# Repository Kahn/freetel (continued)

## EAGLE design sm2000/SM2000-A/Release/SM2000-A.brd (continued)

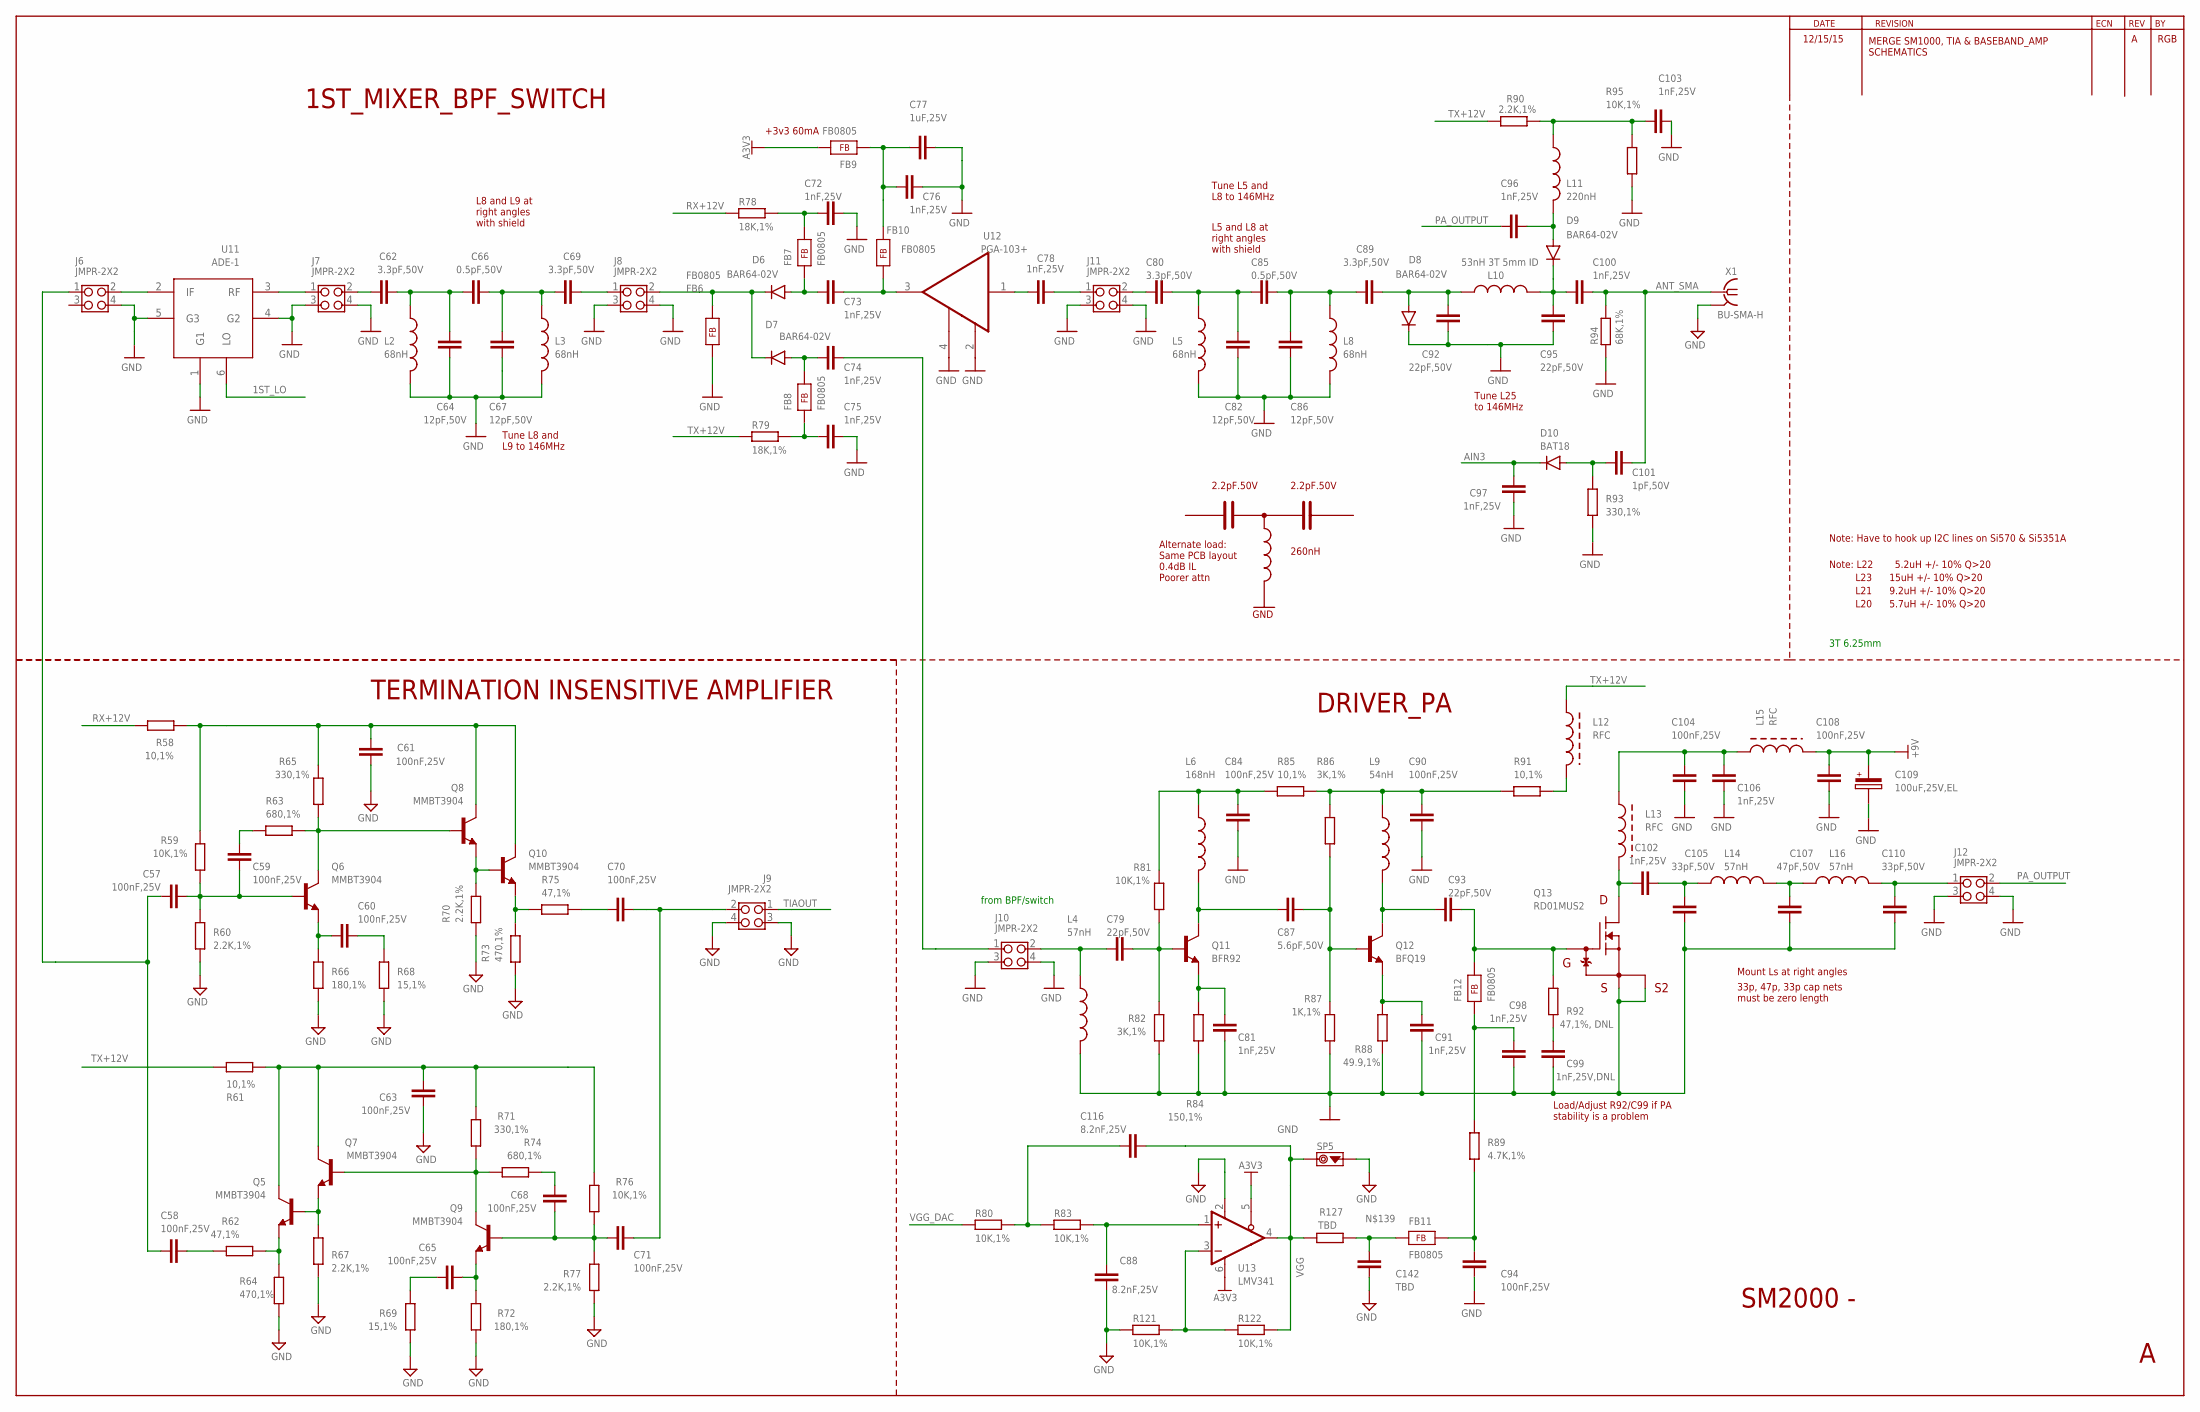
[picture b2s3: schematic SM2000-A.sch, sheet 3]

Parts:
C57, C58, C59, C60, C61, C63, C65, C68, C70, C71, C84, C90, C94, C104, C108: 100nF,25V; C0805
C62, C69, C80, C89: 3.3pF,50V; C0805
C64, C67, C82, C86: 12pF,50V; C0805
C66, C85: 0.5pF,50V; C0805
C72, C73, C74, C75, C76, C78, C81, C91, C96, C97, C98, C100, C102, C103, C106: 1nF,25V; C0805
C77: 1uF,25V; C0805
C79, C92, C93, C95: 22pF,50V; C0805
C87: 5.6pF,50V; C0805
C88, C116: 8.2nF,25V; C0805
C99: 1nF,25V,DNL; C0805
C101: 1pF,50V; C0805
C105, C110: 33pF,50V; C0805
C107: 47pF,50V; C0805
C109: 100uF,25V,EL; CAP-CHEMI-F80
C142: TBD; C0805
D6, D7, D8, D9: BAR64-02V; SC79_INFINEON
D10: BAT18; SOT23
FB6, FB7, FB8, FB9, FB10, FB11, FB12: FB0805; FE0805
J6, J7, J8, J9, J10, J11, J12: JMPR-2X2; JMPR-2X2X.1
L2, L3, L5, L8: 68nH; L10X15
L4, L14, L16: 57nH; L10X15
L6: 168nH; L10X15
L9: 54nH; L10X15
L10: 53nH 3T 5mm ID; L10X15
L11: 220nH; L10X15
L12, L13, L15: RFC; Z15/4
Q5, Q6, Q7, Q8, Q9, Q10: MMBT3904; SOT23
Q11: BFR92; SOT23
Q12: BFQ19; SOT89
Q13: RD01MUS2; SOT89
R58, R61, R85, R91: 10,1%; R0805
R59, R76, R80, R81, R83, R95, R121, R122: 10K,1%; R0805
R60, R67, R70, R77, R90: 2.2K,1%; R0805
R62, R75: 47,1%; R0805
R63, R74: 680,1%; R0805
R64, R73: 470,1%; R0805
R65, R71, R93: 330,1%; R0805
R66, R72: 180,1%; R0805
R68, R69: 15,1%; R0805
R78, R79: 18K,1%; R0805
R82, R86: 3K,1%; R0805
R84: 150,1%; R0805
R87: 1K,1%; R0805
R88: 49.9,1%; R0805
R89: 4.7K,1%; R0805
R92: 47,1%, DNL; R0805
R94: 68K,1%; R0805
R127: TBD; R0805
SP5: SCOPE_PAD
U11: ADE-1
U12: PGA-103+; DF782
U13: LMV341; SOT23-6
X1: BU-SMA-H

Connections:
1ST_LO: U11.6 (LO); also elsewhere on the board
+9V: C108.1, C109.1, L15.2; also elsewhere on the board
A3V3: FB9.2, U13.5 (!SHDN!), U13.6 (V+); also elsewhere on the board
AIN3: C97.2, D10.1 (K); also elsewhere on the board
ANT_SMA: C100.1, C101.2, R94.2, X1.1
DRIVER/PA_INPUT: C74.2, J10.1
GND: C61.2, C63.2, C64.2, C67.1, C72.2, C75.2, C76.2, C77.2, C81.2, C82.2, C84.2, C86.1, C88.2, C90.2, C91.2, C92.2, C94.2, C95.2, C97.1, C98.2, C99.2, C103.2, C104.2, C105.2, C106.2, C107.2, C108.2, C109.2, C110.2, C142.2, D8.C, FB6.1, J6.4, J7.3, J7.4, J8.3, J8.4, J9.3, J9.4, J10.3, J10.4, J11.3, J11.4, J12.3, J12.4, L2.2, L3.2, L4.2, L5.2, L8.2, Q13.2 (S), Q13.4 (S2), R60.1, R64.1, R66.1, R67.1, R68.1, R69.1, R70.1, R72.1, R73.1, R77.1, R82.1, R84.1, R87.1, R88.1, R93.1, R94.1, R95.1, R121.1, SP5.2, U11.1 (G1), U11.4 (G2), U11.5 (G3), U12.2 (GND), U12.4 (GND1), U13.2 (GND), X1.2, X1.3 (2), X1.4 (2), X1.5 (2); also elsewhere on the board
unnamed: C76.1, C77.1, FB9.1, FB10.2
unnamed: R121.2, R122.1, U13.3 (-IN)
unnamed: C107.1, L14.2, L16.1
unnamed: C80.2, J11.2
unnamed: J6.2, U11.2 (IF)
unnamed: L12.2, R91.1
unnamed: C62.1, C64.1, C66.2, L2.1
unnamed: C116.1, R80.2, R83.1
unnamed: C102.1, L13.2, Q13.3 (D)
unnamed: C93.1, FB12.2, Q13.1 (G), R92.2
unnamed: C88.1, R83.2, U13.1 (+IN)
unnamed: C95.1, C100.2, D9.C, L10.2
unnamed: C94.1, FB11.2, R89.1
unnamed: C110.1, J12.1, L16.2
unnamed: C62.2, J7.2
unnamed: C101.1, D10.3 (A), R93.2
unnamed: J7.1, U11.3 (RF)
unnamed: C78.2, J11.1
unnamed: C78.1, U12.1 (1N)
unnamed: C70.1, C71.2, J9.2
unnamed: Q6.3 (C), Q8.1 (B), R63.2, R65.2
unnamed: C61.1, Q8.3 (C), Q10.3 (C), R58.1, R59.2, R65.1
unnamed: Q8.2 (E), Q10.1 (B), R70.2
unnamed: C59.1, R63.1
unnamed: C81.1, Q11.2 (E), R84.2
unnamed: C91.1, Q12.3 (E), R88.2
unnamed: C84.1, L6.1, R81.2, R85.2
unnamed: C90.1, L9.1, R85.1, R86.2, R91.2
unnamed: C87.1, Q12.1 (B), R86.1, R87.2
unnamed: C79.1, Q11.1 (B), R81.1, R82.2
unnamed: C69.1, J8.1
unnamed: C87.2, L6.2, Q11.3 (C)
unnamed: C57.1, C59.2, Q6.1 (B), R59.1, R60.2
unnamed: C93.2, L9.2, Q12.2 (C), Q12.4 (C)
unnamed: C60.1, Q6.2 (E), R66.2
unnamed: C60.2, R68.2
unnamed: Q10.2 (E), R73.2, R75.1
unnamed: C70.2, R75.2
unnamed: Q7.1 (B), Q9.3 (C), R71.2, R74.2
unnamed: C63.1, Q5.3 (C), Q7.3 (C), R61.2, R71.1, R76.2
unnamed: Q5.1 (B), Q7.2 (E), R67.2
unnamed: C68.1, R74.1
unnamed: C68.2, C71.1, Q9.1 (B), R76.1, R77.2
unnamed: C65.1, Q9.2 (E), R72.2
unnamed: C65.2, R69.2
unnamed: Q5.2 (E), R62.1, R64.2
unnamed: C58.2, R62.2
unnamed: C72.1, FB7.2, R78.2
unnamed: C79.2, J10.2, L4.1
unnamed: C99.1, R92.1
unnamed: C98.1, FB12.1, R89.2
unnamed: C73.1, D6.A, FB7.1
unnamed: C73.2, FB10.1, U12.3 (OUT)
unnamed: C74.1, D7.A, FB8.2
unnamed: C102.2, C105.1, L14.1
unnamed: C75.1, FB8.1, R79.2
unnamed: C66.1, C67.2, C69.2, L3.1
unnamed: C104.1, C106.1, L13.1, L15.1
unnamed: D6.C, D7.C, FB6.2, J8.2
unnamed: C80.1, C82.1, C85.2, L5.1
unnamed: C85.1, C86.2, C89.2, L8.1
unnamed: C142.1, FB11.1, R127.1
unnamed: C89.1, C92.1, D8.A, L10.1
unnamed: C96.1, D9.A, L11.2
unnamed: C103.1, L11.1, R90.1, R95.2
PA_OUTPUT: C96.2, J12.2
RX+12V: R58.2, R78.1; also elsewhere on the board
TIAIN: C57.2, C58.1, J6.1
TIAOUT: J9.1; also elsewhere on the board
TX+12V: L12.1, R61.1, R79.1, R90.2; also elsewhere on the board
VGG: C116.2, R122.2, R127.2, SP5.1, U13.4 (OUT)
VGG_DAC: R80.1; also elsewhere on the board

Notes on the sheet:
SM2000 -
12/15/15
MERGE SM1000, TIA & BASEBAND_AMP SCHEMATICS
RGB
3T 6.25mm
Note: L22
5.2uH +/- 10% Q>20
L23 15uH +/- 10% Q>20
L21 9.2uH +/- 10% Q>20
L20 5.7uH +/- 10% Q>20
Note: Have to hook up I2C lines on Si570 & Si5351A
Tune L8 and L9 to 146MHz
+3v3 60mA
Alternate load: Same PCB layout 0.4dB IL Poorer attn
Tune L5 and L8 to 146MHz
L5 and L8 at right angles with shield
L8 and L9 at right angles with shield
Tune L25 to 146MHz
1ST_MIXER_BPF_SWITCH
TERMINATION INSENSITIVE AMPLIFIER
Load/Adjust R92/C99 if PA stability is a problem
from BPF/switch
33p, 47p, 33p cap nets must be zero length
Mount Ls at right angles
DRIVER_PA
GND
2.2pF.50V
260nH

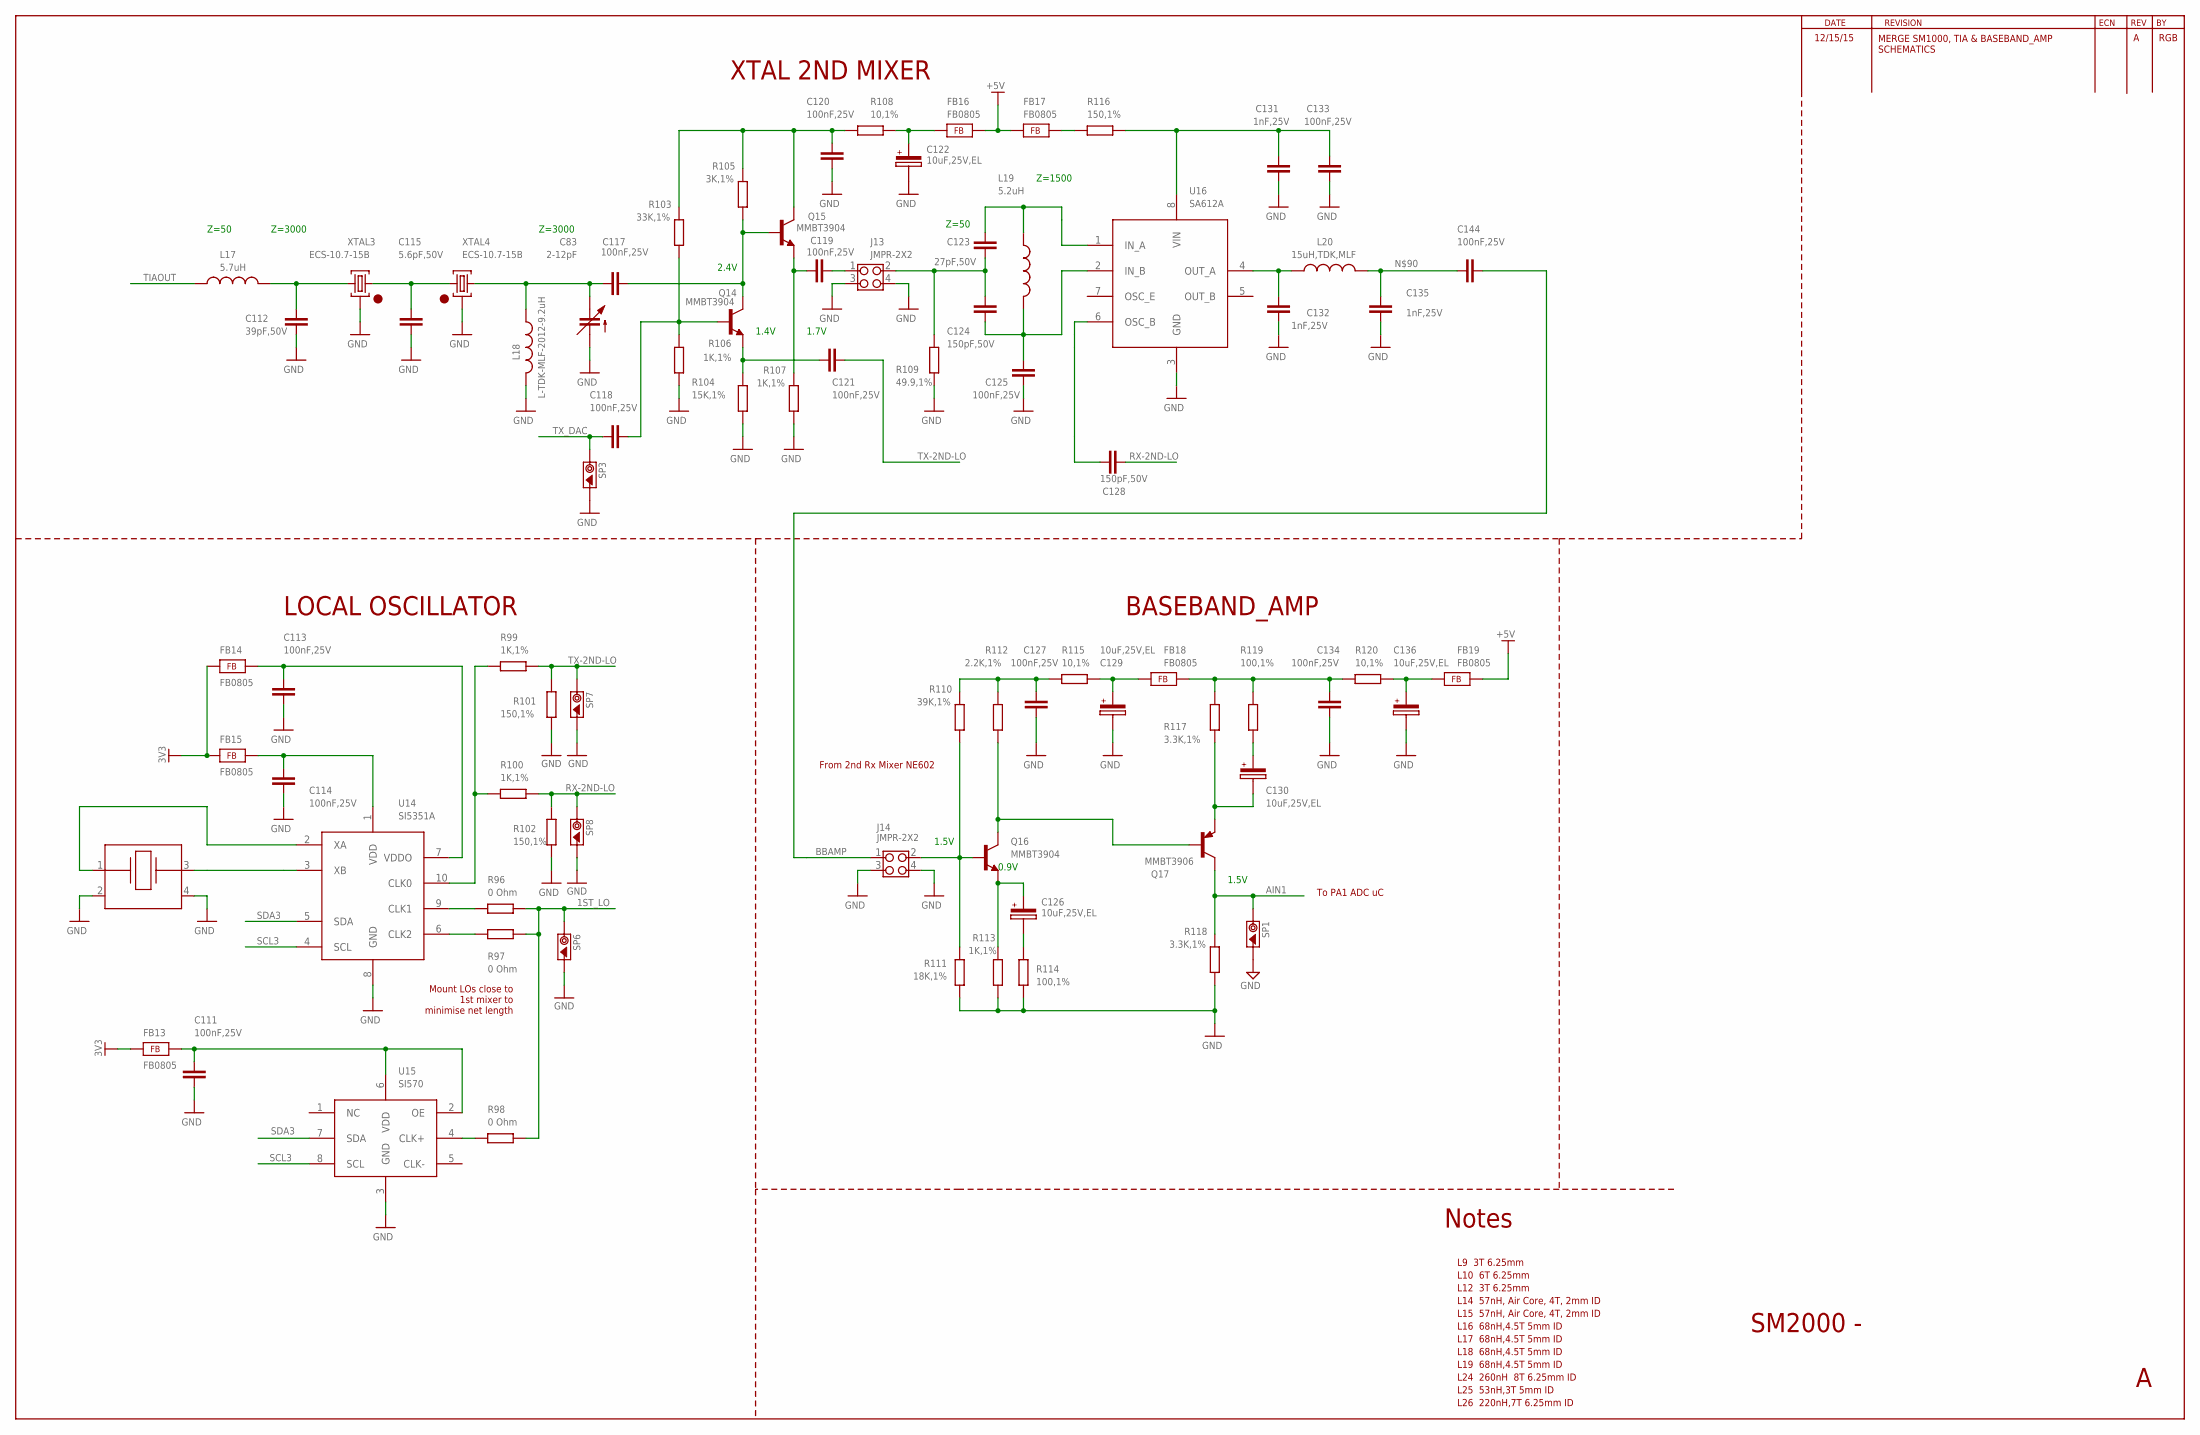
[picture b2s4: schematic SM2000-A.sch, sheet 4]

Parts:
C83: 2-12pF; TRIMCAP_VAR_2222_V
C111, C113, C114, C117, C118, C119, C120, C121, C125, C127, C133, C134, C144: 100nF,25V; C0805
C112: 39pF,50V; C0805
C115: 5.6pF,50V; C0805
C122, C126, C129, C130, C136: 10uF,25V,EL; NICHICON-WJ-5
C123: 27pF,50V; C0805
C124, C128: 150pF,50V; C0805
C131, C132, C135: 1nF,25V; C0805
FB13, FB14, FB15, FB16, FB17, FB18, FB19: FB0805; FE0805
J13, J14: JMPR-2X2; JMPR-2X2X.1
L17: 5.7uH; L-TDK-MLF2012
L18: L-TDK-MLF-2012-9.2uH; L-TDK-MLF2012
L19: 5.2uH; L-TDK-MLF2012
L20: 15uH,TDK,MLF; L-TDK-MLF2012
Q14, Q15, Q16: MMBT3904; SOT23
Q17: MMBT3906; SOT23
R96, R97, R98: 0 Ohm; R0805
R99, R100, R106, R107, R113: 1K,1%; R0805
R101, R102, R116: 150,1%; R0805
R103: 33K,1%; R0805
R104: 15K,1%; R0805
R105: 3K,1%; R0805
R108, R115, R120: 10,1%; R0805
R109: 49.9,1%; R0805
R110: 39K,1%; R0805
R111: 18K,1%; R0805
R112: 2.2K,1%; R0805
R114, R119: 100,1%; R0805
R117, R118: 3.3K,1%; R0805
SP1, SP3, SP6, SP7, SP8: SCOPE_PAD
U14: SI5351A; MSOP10
U15: SI570
U16: SA612A; SO-08
XTAL2: 25.000MHz; CTS-405
XTAL3, XTAL4: ECS-10.7-15B; HC49U

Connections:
1ST_LO: R96.1, R97.1, R98.1, SP6.1; also elsewhere on the board
3V3: FB13.1, FB14.1, FB15.1; also elsewhere on the board
+5V: FB16.2, FB17.1, FB19.2; also elsewhere on the board
AIN1: Q17.3 (C), R118.2, SP1.1; also elsewhere on the board
BBAMP: C144.1, J14.1
GND: C83.R1 (R), C83.R2 (R), C111.2, C112.2, C113.2, C114.2, C115.2, C120.2, C122.2, C125.1, C127.2, C129.2, C131.1, C132.1, C133.1, C134.2, C135.1, C136.2, J13.3, J13.4, J14.3, J14.4, L18.P$2 (2), R101.2, R102.2, R104.1, R106.1, R107.1, R109.1, R111.1, R113.1, R114.1, R118.1, SP1.2, SP3.2, SP6.2, SP7.2, SP8.2, U14.8 (GND), U15.3 (GND), U16.3 (GND), XTAL2.2, XTAL2.4, XTAL3.2, XTAL4.2; also elsewhere on the board
unnamed: U14.2 (XA), XTAL2.1
unnamed: C119.2, J13.1
unnamed: C114.1, FB15.2, U14.1 (VDD)
unnamed: C123.1, C124.2, J13.2, R109.2
unnamed: C124.1, C125.2, L19.P$2 (2), U16.2 (IN_B)
unnamed: U14.3 (XB), XTAL2.3
unnamed: C135.2, C144.2, L20.P$2 (2)
unnamed: C126.1, Q16.2 (E), R113.2
unnamed: C134.1, FB18.2, R117.2, R119.2, R120.2
unnamed: C127.1, R110.2, R112.2, R115.2
unnamed: J14.2, Q16.1 (B), R110.1, R111.2
unnamed: Q16.3 (C), Q17.1 (B), R112.1
unnamed: C130.2, Q17.2 (E), R117.1
unnamed: C129.1, FB18.1, R115.1
unnamed: C126.2, R114.2
unnamed: C130.1, R119.1
unnamed: C136.1, FB19.1, R120.1
unnamed: C111.1, FB13.2, U15.2 (OE), U15.6 (VDD)
unnamed: C113.1, FB14.2, U14.7 (VDDO)
unnamed: R96.2, U14.9 (CLK1)
unnamed: R97.2, U14.6 (CLK2)
unnamed: R98.2, U15.4 (CLK+)
unnamed: R99.2, R100.2, U14.10 (CLK0)
unnamed: C120.1, Q15.3 (C), R103.2, R105.2, R108.2
unnamed: C117.2, Q14.3 (C), Q15.1 (B), R105.1
unnamed: C122.1, FB16.1, R108.1
unnamed: C112.1, L17.P$2 (2), XTAL3.3
unnamed: C115.1, XTAL3.1, XTAL4.1
unnamed: C83.S, C117.1, L18.P$1 (1), XTAL4.3
unnamed: C118.1, Q14.1 (B), R103.1, R104.2
unnamed: C121.1, Q14.2 (E), R106.2
unnamed: C119.1, Q15.2 (E), R107.2
unnamed: C123.2, L19.P$1 (1), U16.1 (IN_A)
unnamed: FB17.2, R116.2
unnamed: C131.2, C133.2, R116.1, U16.8 (VIN)
unnamed: C128.2, U16.6 (OSC_B)
unnamed: C132.2, L20.P$1 (1), U16.4 (OUT_A)
RX-2ND-LO: C128.1, R100.1, R102.1, SP8.1
SCL3: U14.4 (SCL), U15.8 (SCL); also elsewhere on the board
SDA3: U14.5 (SDA), U15.7 (SDA); also elsewhere on the board
TIAOUT: L17.P$1 (1); also elsewhere on the board
TX-2ND-LO: C121.2, R99.1, R101.1, SP7.1
TX_DAC: C118.2, SP3.1; also elsewhere on the board

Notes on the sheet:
12/15/15
MERGE SM1000, TIA & BASEBAND_AMP SCHEMATICS
RGB
SM2000 -
L10 6T 6.25mm
L12 3T 6.25mm
L9 3T 6.25mm
L26 220nH,7T 6.25mm ID
L19 68nH,4.5T 5mm ID
L18 68nH,4.5T 5mm ID
L17 68nH,4.5T 5mm ID
L16 68nH,4.5T 5mm ID
L24 260nH 8T 6.25mm ID
L25 53nH,3T 5mm ID
L15 57nH, Air Core, 4T, 2mm ID
L14 57nH, Air Core, 4T, 2mm ID
1.7V
1.4V
2.4V
Z=50
Z=3000
Z=1500
XTAL 2ND MIXER
Notes
To PA1 ADC uC
From 2nd Rx Mixer NE602
1.5V
0.9V
BASEBAND_AMP
Mount LOs close to 1st mixer to minimise net length
LOCAL OSCILLATOR

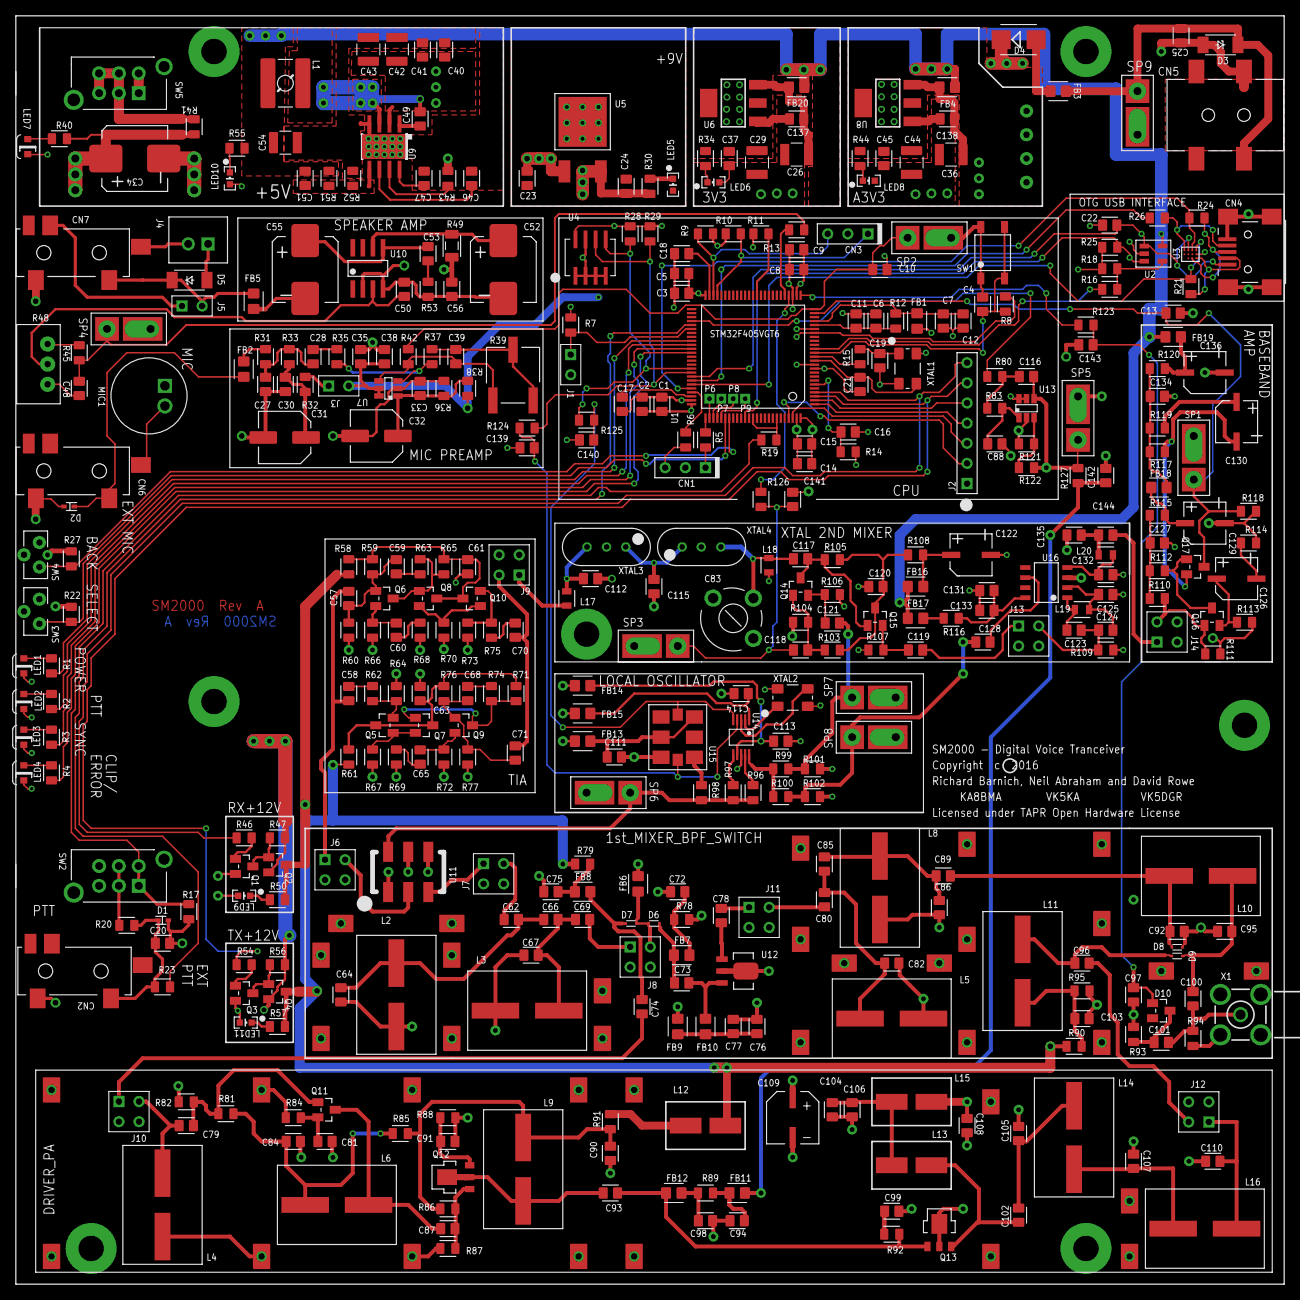
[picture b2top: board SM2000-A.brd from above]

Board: 4 copper layers, 160.0 x 160.0 mm, 456 parts (0 on the bottom side), 227 nets.

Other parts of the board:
DRILEGEND: DRILEGEND

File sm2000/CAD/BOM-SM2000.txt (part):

Bill of Materials from SM2000.sch, 407 parts, grouped by values, as of 1/28/2016 6:16:19 PM

Part	Value			Device			Package
C1	100nF,25V		CAP-0805		C0805			
C3	100nF,25V		CAP-0805		C0805			
C4	100nF,25V		CAP-0805		C0805			
C8	100nF,25V		CAP-0805		C0805			
C11	100nF,25V		CAP-0805		C0805			
C12	100nF,25V		CAP-0805		C0805			
C14	100nF,25V		CAP-0805		C0805			
C20	100nF,25V		CAP-0805		C0805			
C24	100nF,25V		CAP-0805		C0805			
C30	100nF,25V		CAP-0805		C0805			
C33	100nF,25V		CAP-0805		C0805			
C35	100nF,25V		CAP-0805		C0805			
C37	100nF,25V		CAP-0805		C0805			
C41	100nF,25V		CAP-0805		C0805			
C45	100nF,25V		CAP-0805		C0805			
C48	100nF,25V		CAP-0805		C0805			
C49	100nF,25V		CAP-0805		C0805			
C56	100nF,25V		CAP-0805		C0805			
C57	100nF,25V		CAP-0805		C0805			
C58	100nF,25V		CAP-0805		C0805			
C59	100nF,25V		CAP-0805		C0805			
C60	100nF,25V		CAP-0805		C0805			
C61	100nF,25V		CAP-0805		C0805			
C63	100nF,25V		CAP-0805		C0805			
C65	100nF,25V		CAP-0805		C0805			
C68	100nF,25V		CAP-0805		C0805			
C70	100nF,25V		CAP-0805		C0805			
C71	100nF,25V		CAP-0805		C0805			
C137	100nF,25V		CAP-0805		C0805			
C138	100nF,25V		CAP-0805		C0805
C2	10nF,25V		CAP-0805		C0805			
C5	10nF,25V		CAP-0805		C0805			
C9	10nF,25V		CAP-0805		C0805			
C15	10nF,25V		CAP-0805		C0805			
C25	10nF,25V		CAP-0805		C0805
C6	1uF,25V			CAP-0805		C0805			
C7	1uF,25V			CAP-0805		C0805			
C77	1uF,25V			CAP-0805		C0805
C10	1nF,25V			CAP-0805		C0805			
C13	1nF,25V			CAP-0805		C0805			
C27	1nF,25V			CAP-0805		C0805			
C40	1nF,25V			CAP-0805		C0805			
C72	1nF,25V			CAP-0805		C0805			
C73	1nF,25V			CAP-0805		C0805			
C74	1nF,25V			CAP-0805		C0805			
C75	1nF,25V			CAP-0805		C0805			
C76	1nF,25V			CAP-0805		C0805			
C78	1nF,25V			CAP-0805		C0805			
C81	1nF,25V			CAP-0805		C0805			
C91	1nF,25V			CAP-0805		C0805			
C96	1nF,25V			CAP-0805		C0805			
C97	1nF,25V			CAP-0805		C0805			
C98	1nF,25V			CAP-0805		C0805			
C100	1nF,25V			CAP-0805		C0805			
C102	1nF,25V			CAP-0805		C0805			
C103	1nF,25V			CAP-0805		C0805			
C106	1nF,25V			CAP-0805		C0805			
C131	1nF,25V			CAP-0805		C0805			
C132	1nF,25V			CAP-0805		C0805			
C135	1nF,25V			CAP-0805		C0805
C16	1uF,16V			CAP-0805		C0805
C17	2.2uF,25V		CAP-0805		C0805			
C18	2.2uF,25V		CAP-0805		C0805			
C38	2.2uF,25V		CAP-0805		C0805
C19	20pF,50V		CAP-0805		C0805			
C21	20pF,50V		CAP-0805		C0805			
C51	20pF,50V		CAP-0805		C0805
C22	4.7uF,25V		CAP-0805		C0805
C23	.33uF,25V		CAP-0805		C0805
C26	22uF,25V		CAP-1210		C1210			
C29	22uF,25V		CAP-1210		C1210			
C36	22uF,25V		CAP-1210		C1210			
C42	22uF,25V		CAP-1210		C1210			
C43	22uF,25V		CAP-1210		C1210			
C44	22uF,25V		CAP-1210		C1210
C28	220nF,25V		CAP-0805		C0805
C31	100uF,6.3V,EL		NICHICON-WX-6.3		NICHICON-WX-6.3		
C32	100uF,6.3V,EL		NICHICON-WX-6.3		NICHICON-WX-6.3
C34	220uF,25V		CAP-CHEMI-MVE-HA0	CAP-CHEMI-HA0		
C52	220uF,25V		CAP-CHEMI-MVE-HA0	CAP-CHEMI-HA0		
C55	220uF,25V		CAP-CHEMI-MVE-HA0	CAP-CHEMI-HA0
C39	100pF,50V		CAP-0805		C0805
C46	470nF,25V		CAP-0805		C0805
C47	8.2nF,25V		CAP-0805		C0805
C50	3.9nF,25V		CAP-0805		C0805
C53	47nF,25V		CAP-0805		C0805
C54	22uF,25V,1210		CAPACITOR_1210		CAPC3225X168N
C62	3.3pF,50V		CAP-0805		C0805			
C69	3.3pF,50V		CAP-0805		C0805			
C80	3.3pF,50V		CAP-0805		C0805			
C89	3.3pF,50V		CAP-0805		C0805
C64	12pF.50V		CAP-0805		C0805
C66	0.5pF,50V		CAP-0805		C0805			
C85	0.5pF,50V		CAP-0805		C0805
C67	12pF,50V		CAP-0805		C0805			
C82	12pF,50V		CAP-0805		C0805			
C86	12pF,50V		CAP-0805		C0805
C79	22pF,50V		CAP-0805		C0805			
C92	22pF,50V		CAP-0805		C0805			
C93	22pF,50V		CAP-0805		C0805			
C95	22pF,50V		CAP-0805		C0805
C83	2.2pF,50V		CAP-0805		C0805			
C88	2.2pF,50V		CAP-0805		C0805
C84	0.1uF.25V		CAP-0805		C0805			
C90	0.1uF.25V		CAP-0805		C0805			
C94	0.1uF.25V		CAP-0805		C0805			
C104	0.1uF.25V		CAP-0805		C0805			
C108	0.1uF.25V		CAP-0805		C0805			
C125	0.1uF.25V		CAP-0805		C0805
C87	5.6pF,50V		CAP-0805		C0805			
C115	5.6pF,50V		CAP-0805		C0805
C99	1nF,25V,DNL		CAP-0805		C0805
C101	1pF,50V			CAP-0805		C0805
C105	33pF,50V		CAP-0805		C0805			
C110	33pF,50V		CAP-0805		C0805
C107	47pF,50V		CAP-0805		C0805
C109	100uF,25V,EL		CAP-CHEMI-F80		CAP-CHEMI-F80
C111	0.1uF,25V		CAP-0805		C0805			
C113	0.1uF,25V		CAP-0805		C0805			
C114	0.1uF,25V		CAP-0805		C0805			
C117	0.1uF,25V		CAP-0805		C0805			
C118	0.1uF,25V		CAP-0805		C0805			
C119	0.1uF,25V		CAP-0805		C0805			
C120	0.1uF,25V		CAP-0805		C0805			
C121	0.1uF,25V		CAP-0805		C0805			
C127	0.1uF,25V		CAP-0805		C0805			
C133	0.1uF,25V		CAP-0805		C0805			
C134	0.1uF,25V		CAP-0805		C0805
C112	39pF,50V		CAP-0805		C0805
C116	2-12pF			C-TRIMM3008		3008
C122	10uF,25V,EL		CAP-10UF-WJ5		NICHICON-WJ-5		
C126	10uF,25V,EL		CAP-10UF-WJ5		NICHICON-WJ-5		
C129	10uF,25V,EL		CAP-10UF-WJ5		NICHICON-WJ-5		
C130	10uF,25V,EL		CAP-10UF-WJ5		NICHICON-WJ-5		
C136	10uF,25V,EL		CAP-10UF-WJ5		NICHICON-WJ-5
C123	27pF,50V		CAP-0805		C0805
C124	150pF,50V		CAP-0805		C0805			
C128	150pF,50V		CAP-0805		C0805
CN1	HDR100-3		HDR100-3		HDR100-3		
CN3	HDR100-3		HDR100-3		HDR100-3
CN2	ST-3509			ST-3509			ST-3509			
CN6	ST-3509			ST-3509			ST-3509			
CN7	ST-3509			ST-3509			ST-3509
CN4	JS-MU3-002		JS-MU3-002		JI-MU3-002
CN5	DS-0518			DS-0518			DS-0518
D1	DNL			PESD5ZX			SOD523			
D2	DNL			PESD5ZX			SOD523
D3	PTVS20VP1UP		PTVS20VP1UP		SOD128
D4	BAT60J			BAT60J			SOD323R_INFINEON
D5	DNL			PTVS20VP1UP		SOD128
D6	BAR64-02V		BAR64-02V		SC79_INFINEON		
D7	BAR64-02V		BAR64-02V		SC79_INFINEON		
D8	BAR64-02V		BAR64-02V		SC79_INFINEON		
D9	BAR64-02V		BAR64-02V		SC79_INFINEON
D10	BAT18			BAT18			SOT23
FB1	FB0805			FB0805			FE0805			
FB2	FB0805			FB0805			FE0805			
FB3	FB0805			FB0805			FE0805			
FB4	FB0805			FB0805			FE0805			
FB5	FB0805			FB0805			FE0805			
FB6	FB0805			FB0805			FE0805			
FB7	FB0805			FB0805			FE0805			
FB8	FB0805			FB0805			FE0805			
FB9	FB0805			FB0805			FE0805			
FB10	FB0805			FB0805			FE0805			
FB11	FB0805			FB0805			FE0805			
FB12	FB0805			FB0805			FE0805			
FB13	FB0805			FB0805			FE0805			
FB14	FB0805			FB0805			FE0805			
FB15	FB0805			FB0805			FE0805			
FB16	FB0805			FB0805			FE0805			
FB17	FB0805			FB0805			FE0805			
FB18	FB0805			FB0805			FE0805			
FB19	FB0805			FB0805			FE0805			
FB20	FB0805			FB0805			FE0805
J1	JMP-2PIN		JMP-2PIN		JMPR-2PIN		
J3	JMP-2PIN		JMP-2PIN		JMPR-2PIN		
J5	JMP-2PIN		JMP-2PIN		JMPR-2PIN
J2	HDR100-7		HDR100-7		HDR100-7
J4	CONN-BOOM-XH-2A		CONN-BOOM-XH-2A		CONN-BOOM-XH-2A
J6	JMPR-2X2		JMPR-2X2		JMPR-2X2X.1		
J7	JMPR-2X2		JMPR-2X2		JMPR-2X2X.1		
J8	JMPR-2X2		JMPR-2X2		JMPR-2X2X.1		
J9	JMPR-2X2		JMPR-2X2		JMPR-2X2X.1		
J10	JMPR-2X2		JMPR-2X2		JMPR-2X2X.1		
J11	JMPR-2X2		JMPR-2X2		JMPR-2X2X.1		
J12	JMPR-2X2		JMPR-2X2		JMPR-2X2X.1		
J13	JMPR-2X2		JMPR-2X2		JMPR-2X2X.1		
J14	JMPR-2X2		JMPR-2X2		JMPR-2X2X.1
L1	4.2uH			SRR5028			SRR5028
L2	68nH			L-ROWE_15X10		L10X15			
L3	68nH			L-ROWE_15X10		L10X15			
L5	68nH			L-ROWE_15X10		L10X15			
L8	68nH			L-ROWE_15X10		L10X15
L4	57nH			L-ROWE_15X10		L10X15			
L14	57nH			L-ROWE_15X10		L10X15			
L16	57nH			L-ROWE_15X10		L10X15
L6	168nH			L-ROWE_15X10		L10X15
L7	260nH			L-US0204/5		0204/5
L9	54nH			L-ROWE_15X10		L10X15
L10	53nH 3T 5mm ID		L-ROWE_15X10		L10X15
L11	220nH			L-ROWE_15X10		L10X15
L12	RFC			RFC			Z15/4			
L13	RFC			RFC			Z15/4			
L15	RFC			RFC			Z15/4
L17	5.7uH			L-TDK-MLF-2012		L-TDK-MLF2012
L18	L-TDK-MLF-2012-9.2uH	L-TDK-MLF-2012		L-TDK-MLF2012
L19	5.2uH			L-TDK-MLF-2012		L-TDK-MLF2012
L20	15uH			L-TDK-MLF-2012		L-TDK-MLF2012
LED1	LTST-S220KGKT		LTST-S220K		LTST-S2200K		
LED3	LTST-S220KGKT		LTST-S220K		LTST-S2200K
LED2	LTST-S220KRKT		LTST-S220K		LTST-S2200K		
LED4	LTST-S220KRKT		LTST-S220K		LTST-S2200K
LED5	SML-LX0603GW		SML-LX0603SRW		SML-LX0603SRW		
LED6	SML-LX0603GW		SML-LX0603SRW		SML-LX0603SRW		
LED7	SML-LX0603GW		SML-LX0603SRW		SML-LX0603SRW		
LED8	SML-LX0603GW		SML-LX0603SRW		SML-LX0603SRW		
LED10	SML-LX0603GW		SML-LX0603SRW		SML-LX0603SRW
LED9	SML-LX0603SRW		SML-LX0603SRW		SML-LX0603SRW
LED11	SML-LX0603YW		SML-LX0603SRW		SML-LX0603SRW
MIC1	CMA-4544PF-W		CMA-4544PF-W		CMA-4544PF-W
P1	TPAD50			TPAD50			TPAD50			
P2	TPAD50			TPAD50			TPAD50			
P3	TPAD50			TPAD50			TPAD50			
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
